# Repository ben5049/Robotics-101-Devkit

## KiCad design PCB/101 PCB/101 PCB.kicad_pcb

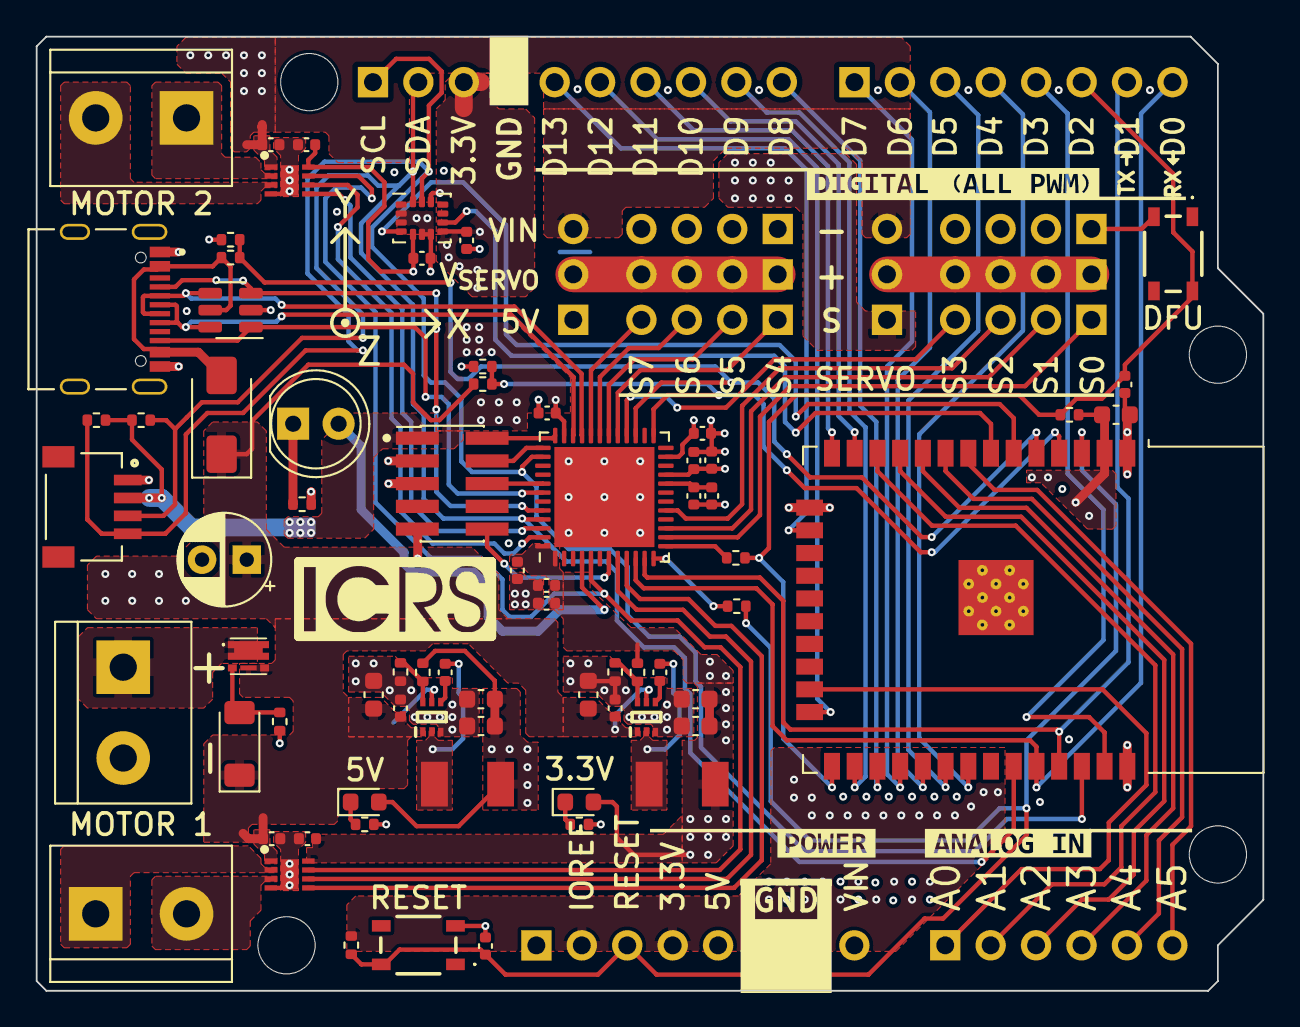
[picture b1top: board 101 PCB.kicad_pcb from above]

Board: 4 copper layers, 68.6 x 53.3 mm, 84 parts (1 on the bottom side), 74 nets.

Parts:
A101: Arduino_UNO_R3; ICRS_101_UNO_R3_NO_PINS
C1, C101, C102, C107, C108, C111, C112, C113, C114, C115, C116, C117, C118, C120, C121, C122, C123, C126: 100n; C_0402_1005Metric
C2, C103, C104, C105, C106, C109, C110: 22u; C_0603_1608Metric
C119: 47u; CP_Radial_D5.0mm_P2.50mm
C124: 4u7; C_0402_1005Metric
C125, C127: 1u; C_0402_1005Metric
D1: LED_R; LED_D5.0mm
D2: SK34
D101, D102: GREEN; LED_0603_1608Metric
D104: ZMM10V; D_MiniMELF
IC101, IC103: TPS563202DRLR; SOTFL50P160X60-6N
IC104, IC105: DRV8837DSGR; SON50P200X200X80-9N
J1: Conn_01x10; PinHeader_1x10_P2.54mm_Vertical
J2: Conn_ARM_JTAG_SWD_10; PinHeader_2x05_P1.27mm_Vertical_SMD
J3, J4: Conn_01x08; PinHeader_1x08_P2.54mm_Vertical
J5: Conn_01x06; PinHeader_1x06_P2.54mm_Vertical
J101: TYPE-C-31-M-12; HRO_TYPE-C-31-M-12
J102, J103, J110: Screw_Terminal_01x02; TerminalBlock_bornier-2_P5.08mm
J104, J105, J106, J107, J108, J109: Conn_01x04; PinHeader_1x04_P2.54mm_Vertical
J111: SM04B-SRSS-TB(LF)(SN); JST_SM04B-SRSS-TB(LF)(SN)
JP101, JP102: Jumper_3_Bridged12; PinHeader_1x03_P2.54mm_Vertical
L101: 4u7; L_Chilisin_BMRA00040415
L102: 3u3; L_Chilisin_BMRA00040415
Q101: DMP3028LFDE; DMP2066UFDE7
R1, R107, R109, R111: 10k; R_0402_1005Metric
R2, R3, R106, R108, R114: 330R; R_0402_1005Metric
R4, R5: 2k2; R_0402_1005Metric
R101: 27k; R_0402_1005Metric
R102, R105: 5k1; R_0402_1005Metric
R103: 1k2; R_0402_1005Metric
R104: 16k; R_0402_1005Metric
R110, R112: 1k; R_0402_1005Metric
S101, S102: TS20-42-25-WT-160-SMT-TR; TS204225WT160SMTTRMSL
U101: ESP32-WROOM-32
U103: USBLC6-4SC6-ES; SOT-23-6
U104: LSM6DS3; LGA-14_3x2.5mm_P0.5mm_LayoutBorder3x4y
U106: STM32G431CBUx; QFN-48-1EP_7x7mm_P0.5mm_EP5.6x5.6mm

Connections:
+3.3V: C2.1, C109.1, C110.1, C111.1, C112.1, C113.1, C115.1, C117.1, C120.1, C121.1, C122.1, C123.1, C124.1, C125.1, D102.2 (A), IC104.8 (VCC), IC105.8 (VCC), J1.3, J2.1 (VTref), J4.2, J4.4, J111.2, L102.2, R1.2, R4.2, R5.2, R104.1, R107.2, U101.2 (VDD), U104.5 (VDDIO), U104.8 (VDD), U104.12 (CS), U106.1 (VBAT), U106.21 (VDDA), U106.23 (VDD), U106.35 (VDD), U106.48 (VDD)
+5V: C103.1, C104.1, D101.2 (A), J4.5, JP101.1 (A), JP102.1 (A), L101.2, R101.1
+BATT: J110.1, Q101.1 (D_1), Q101.2 (D_2), Q101.5 (D_3), Q101.6 (D_4), Q101.8 (D_5)
/3V3_BST: C108.1, IC103.4 (BST)
/3V3_FB: IC103.6 (FB), R104.2, R105.1
/3V3_LED_K: D102.1 (K), R106.1
/3V3_SW: C108.2, IC103.2 (SW), L102.1
/5V_BST: C101.1, IC101.4 (BST)
/5V_FB: IC101.6 (FB), R101.2, R102.1
/5V_LED_K: D101.1 (K), R103.1
/5V_SW: C101.2, IC101.2 (SW), L101.1
/M1_OUT1: IC104.2 (OUT1), J102.1
/M1_OUT2: IC104.3 (OUT2), J102.2
/M2_OUT1: IC105.2 (OUT1), J103.1
/M2_OUT2: IC105.3 (OUT2), J103.2
/RP_PMOS_G: D104.2 (A), Q101.3 (G), R108.1
/STM32_EN: R114.1, U106.12 (PA4)
/STM32_IO0: R2.1, U106.13 (PA5)
/STM_LED_A: D1.2 (A), U106.4 (PC15)
/STM_LED_K: D1.1 (K), R3.2
CC1: J101.A5 (CC1), U103.3 (IO2), U106.44 (PB6)
CC2: J101.B5 (CC2), U103.1 (IO1), U106.42 (PB4)
EN: C118.1, J4.3, R107.1, R114.2, S101.2 (NO_2), U101.3 (EN)
ESP32_RX: J3.8, U101.34 (RXD0/IO3), U106.10 (PA2)
ESP32_TX: J3.7, U101.35 (TXD0/IO1), U106.11 (PA3)
GND: C1.2, C2.2, C102.2, C103.2, C104.2, C105.2, C106.2, C107.2, C109.2, C110.2, C111.2, C112.2, C113.2, C114.2, C115.2, C116.2, C117.2, C118.2, C119.2, C120.2, C121.2, C122.2, C123.2, C124.2, C125.2, C126.2, C127.2, IC101.3 (GND), IC103.3 (GND), IC104.4 (GND), IC104.9 (GND), IC105.4 (GND), IC105.9 (GND), J1.4, J2.3 (GND), J2.5 (GND), J2.9 (GNDDetect), J4.6, J4.7, J101.A1_B12 (GND), J101.B1_A12 (GND), J108.1, J108.2, J108.3, J108.4, J109.1, J109.2, J109.3, J109.4, J110.2, J111.1, R3.1, R102.2, R103.2, R105.2, R106.2, R108.2, R110.2, R112.2, S101.3 (COM_1), S102.3 (COM_1), U101.1 (GND), U101.15 (GND), U101.38 (GND), U101.39 (GND), U103.2 (GND), U104.1 (SDO/SA0), U104.2 (SDX), U104.3 (SCX), U104.6 (GND), U104.7 (GND), U106.49 (VSS)
GPIO2: J1.6, U101.24 (IO2)
GPIO4: J1.9, U101.26 (IO4)
GPIO5: J3.2, U101.29 (IO5)
GPIO12: J1.7, U101.14 (IO12)
GPIO13: J1.5, U101.16 (IO13)
GPIO14: J1.8, U101.13 (IO14)
GPIO15: J5.1, U101.23 (IO15)
GPIO16: J1.10, U101.27 (IO16)
GPIO17: J3.1, U101.28 (IO17)
GPIO18: J3.3, U101.30 (IO18)
GPIO19: J3.4, U101.31 (IO19)
GPIO23: J3.5, U101.37 (IO23)
GPIO25: J5.4, U101.10 (IO25)
GPIO26: J5.3, U101.11 (IO26)
GPIO27: J5.2, U101.12 (IO27)
GPIO32: J5.6, U101.8 (IO32)
GPIO33: J5.5, U101.9 (IO33)
IMU_INT1: U101.6 (IO34), U104.4 (INT1)
IMU_INT2: U101.7 (IO35), U104.9 (INT2)
IO0: C1.1, J3.6, R1.1, R2.2, S102.2 (NO_2), U101.25 (IO0)
M1_IN1: IC104.6 (IN1), U106.8 (PA0)
M1_IN2: IC104.5 (IN2), U106.9 (PA1)
M2_IN1: IC105.6 (IN1), U106.47 (PB9)
M2_IN2: IC105.5 (IN2), U106.46 (PB8)
MOTOR_SLEEP: IC104.7 (~SLEEP), IC105.7 (~SLEEP), U106.5 (PF0)
NRST: J2.10 (~RESET), U106.7 (PG10)
S0: J104.1, U106.14 (PA6)
S1: J104.2, U106.15 (PA7)
S2: J104.3, U106.17 (PB0)
S3: J104.4, U106.28 (PB15)
S4: J105.1, U106.29 (PC6)
S5: J105.2, U106.30 (PA8)
S6: J105.3, U106.31 (PA9)
S7: J105.4, U106.32 (PA10)
SCL: J1.1, J111.4, R5.1, U101.36 (IO22), U104.13 (SCL), U106.38 (PA15)
SDA: J1.2, J111.3, R4.1, U101.33 (IO21), U104.14 (SDA), U106.45 (PB7)
SWCLK: J2.4 (SWDCLK/TCK), U106.37 (PA14)
SWDIO: J2.2 (SWDIO/TMS), U106.36 (PA13)
SWO: J2.6 (SWO/TDO), U106.41 (PB3)
USB_DN: J101.A7 (DN1), J101.B7 (DN2), U103.4 (IO3), U106.33 (PA11)
USB_DP: J101.A6 (DP1), J101.B6 (DP2), U103.6 (IO4), U106.34 (PA12)
VBUS: D2.2 (A), J101.A4_B9 (VBUS), J101.B4_A9 (VBUS), R109.1, U103.5 (VBUS)
VBUS/11: R109.2, R110.1, U101.5 (SENSOR_VN), U106.27 (PB14)
VDDIO1: J106.1, J106.2, J106.3, J106.4, JP101.2 (C)
VDDIO2: J107.1, J107.2, J107.3, J107.4, JP102.2 (C)
VIN: C102.1, C105.1, C106.1, C107.1, C114.1, C116.1, C119.1, D2.1 (K), D104.1 (K), IC101.1 (VIN), IC101.5 (EN), IC103.1 (VIN), IC103.5 (EN), IC104.1 (VM), IC105.1 (VM), J4.8, JP101.3 (B), JP102.3 (B), Q101.4 (S_1), Q101.7 (S_2), R111.1
VIN/11: R111.2, R112.1, U101.4 (SENSOR_VP), U106.25 (PB12)
VREF+: C126.1, C127.1, U106.20 (VREF+)

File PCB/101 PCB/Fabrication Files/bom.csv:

Designator,Footprint,Quantity,Value,JLCPCB Part #（optional）
"C1, C101, C102, C107, C108, C111, C112, C113, C114, C115, C116, C117, C118, C120, C121, C122, C123, C126",402,18,100n,
"C103, C104, C105, C106, C109, C110, C2",603,7,22u,
C124,402,1,4u7,
"C125, C127",402,2,1u,
"D101, D102",603,2,GREEN,C965804
D104,D_MiniMELF,1,ZMM10V,C2891751
D2,SK34,1,SK34,C5140034
"IC101, IC103",SOTFL50P160X60-6N,2,TPS563202DRLR,C1513007
"IC104, IC105",SON50P200X200X80-9N,2,DRV8837DSGR,C39159
J1,PinHeader_1x10_P2.54mm_Vertical,1,Conn_01x10,C2905418
J101,HRO_TYPE-C-31-M-12,1,TYPE-C-31-M-12,C2765186
"J104, J105, J106, J107, J108, J109",PinHeader_1x04_P2.54mm_Vertical,6,Conn_01x04,C6332197
J111,JST_SM04B-SRSS-TB(LF)(SN),1,SM04B-SRSS-TB(LF)(SN),C7430446
J2,PinHeader_2x05_P1.27mm_Vertical_SMD,1,Conn_ARM_JTAG_SWD_10,C2881910
"J3, J4",PinHeader_1x08_P2.54mm_Vertical,2,Conn_01x08,C27438
J5,PinHeader_1x06_P2.54mm_Vertical,1,Conn_01x06,C40877
"JP101, JP102",PinHeader_1x03_P2.54mm_Vertical,2,Jumper_3_Bridged12,C2937625
L101,L_Chilisin_BMRA00040415,1,4u7,C3040385
L102,L_Chilisin_BMRA00040415,1,3u3,C3040384
Q101,DMP2066UFDE7,1,DMP3028LFDE,C150441
"R1, R107, R109, R111",402,4,10k,
R101,402,1,27k,
"R102, R105",402,2,5k1,
R103,402,1,1k2,
R104,402,1,16k,
"R106, R108, R114, R2, R3",402,5,330R,
"R110, R112",402,2,1k,
"R4, R5",402,2,2k2,
"S101, S102",TS204225WT160SMTTRMSL,2,TS20-42-25-WT-160-SMT-TR,C139797
U101,ESP32-WROOM-32,1,ESP32-WROOM-32,C701342
U103,SOT-23-6,1,USBLC6-4SC6-ES,C5180279
U104,LGA-14_3x2.5mm_P0.5mm_LayoutBorder3x4y,1,LSM6DS3,C967633
U106,QFN-48-1EP_7x7mm_P0.5mm_EP5.6x5.6mm,1,STM32G431CBUx,C529356

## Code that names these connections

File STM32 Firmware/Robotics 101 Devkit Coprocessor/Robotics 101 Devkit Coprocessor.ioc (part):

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Mcu.Name=STM32G431C(6-8-B)Ux
Mcu.Package=UFQFPN48
Mcu.UserName=STM32G431CBUx
PA0.Signal=S_TIM2_CH1
PA1.Signal=S_TIM2_CH2
PA11.Mode=Device
PA11.Signal=USB_DM
PA12.Mode=Device
PA12.Signal=USB_DP
PA13.Mode=Trace_Asynchronous_SW
PA13.Signal=SYS_JTMS-SWDIO
PA14.Mode=Trace_Asynchronous_SW
PA14.Signal=SYS_JTCK-SWCLK
PA15.Mode=I2C
PA15.Signal=I2C1_SCL
PA2.Mode=Asynchronous
PA2.Signal=USART2_TX
PA3.Mode=Asynchronous
PA3.Signal=USART2_RX
PA4.Mode=NSS_Signal_Hard_Output
PA4.Signal=SPI3_NSS
PA6.Signal=S_TIM3_CH1
PA7.Signal=S_TIM3_CH2
PB0.Signal=S_TIM3_CH3
PB1.Signal=S_TIM3_CH4
PB10.Signal=S_TIM2_CH3
PB11.Signal=S_TIM2_CH4
PB15.Mode=IN15-Single-Ended
PB15.Signal=ADC2_IN15
PB3.Mode=Trace_Asynchronous_SW
PB3.Signal=SYS_JTDO-SWO
PB4.Mode=Sink_AllSignals
PB4.Signal=UCPD1_CC2
PB5.Mode=Full_Duplex_Master
PB5.Signal=SPI3_MOSI
PB6.Mode=Sink_AllSignals
PB6.Signal=UCPD1_CC1
PB7.Mode=I2C
PB7.Signal=I2C1_SDA
PB8-BOOT0.Signal=S_TIM8_CH2
PB9.Signal=S_TIM8_CH3
PC10.Mode=Full_Duplex_Master
PC10.Signal=SPI3_SCK
PC11.Mode=Full_Duplex_Master
PC11.Signal=SPI3_MISO
PC13.Mode=PWM Generation4 CH4N
PC13.Signal=TIM8_CH4N
PC6.Signal=S_TIM8_CH1
PF0-OSC_IN.Mode=IN10-Single-Ended
PF0-OSC_IN.Signal=ADC1_IN10
RCC.HSE_VALUE=8000000
RCC.SYSCLKFreq_VALUE=144000000
RCC.SYSCLKSource=RCC_SYSCLKSOURCE_PLLCLK
board=custom

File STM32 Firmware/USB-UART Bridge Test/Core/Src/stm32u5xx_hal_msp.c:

/* USER CODE BEGIN Header */
/**
  ******************************************************************************
  * @file         stm32u5xx_hal_msp.c
  * @brief        This file provides code for the MSP Initialization
  *               and de-Initialization codes.
  ******************************************************************************
  * @attention
  *
  * Copyright (c) 2023 STMicroelectronics.
  * All rights reserved.
  *
  * This software is licensed under terms that can be found in the LICENSE file
  * in the root directory of this software component.
  * If no LICENSE file comes with this software, it is provided AS-IS.
  *
  ******************************************************************************
  */
/* USER CODE END Header */

/* Includes ------------------------------------------------------------------*/
#include "main.h"
/* USER CODE BEGIN Includes */

/* USER CODE END Includes */

/* Private typedef -----------------------------------------------------------*/
/* USER CODE BEGIN TD */

/* USER CODE END TD */

/* Private define ------------------------------------------------------------*/
/* USER CODE BEGIN Define */

/* USER CODE END Define */

/* Private macro -------------------------------------------------------------*/
/* USER CODE BEGIN Macro */

/* USER CODE END Macro */

/* Private variables ---------------------------------------------------------*/
/* USER CODE BEGIN PV */

/* USER CODE END PV */

/* Private function prototypes -----------------------------------------------*/
/* USER CODE BEGIN PFP */

/* USER CODE END PFP */

/* External functions --------------------------------------------------------*/
/* USER CODE BEGIN ExternalFunctions */

/* USER CODE END ExternalFunctions */

/* USER CODE BEGIN 0 */

/* USER CODE END 0 */
/**
  * Initializes the Global MSP.
  */
void HAL_MspInit(void)
{
  /* USER CODE BEGIN MspInit 0 */

  /* USER CODE END MspInit 0 */

  __HAL_RCC_PWR_CLK_ENABLE();

  HAL_NVIC_SetPriorityGrouping(NVIC_PRIORITYGROUP_3);

  /* System interrupt init*/

  /* USER CODE BEGIN MspInit 1 */

  /* USER CODE END MspInit 1 */
}

/**
* @brief ADC MSP Initialization
* This function configures the hardware resources used in this example
* @param hadc: ADC handle pointer
* @retval None
*/
void HAL_ADC_MspInit(ADC_HandleTypeDef* hadc)
{
  GPIO_InitTypeDef GPIO_InitStruct = {0};
  RCC_PeriphCLKInitTypeDef PeriphClkInit = {0};
  if(hadc->Instance==ADC1)
  {
  /* USER CODE BEGIN ADC1_MspInit 0 */

  /* USER CODE END ADC1_MspInit 0 */

  /** Initializes the peripherals clock
  */
    PeriphClkInit.PeriphClockSelection = RCC_PERIPHCLK_ADCDAC;
    PeriphClkInit.AdcDacClockSelection = RCC_ADCDACCLKSOURCE_HSI;
    if (HAL_RCCEx_PeriphCLKConfig(&PeriphClkInit) != HAL_OK)
    {
      Error_Handler();
    }

    /* Peripheral clock enable */
    __HAL_RCC_ADC12_CLK_ENABLE();

    __HAL_RCC_GPIOC_CLK_ENABLE();
    /**ADC1 GPIO Configuration
    PC2     ------> ADC1_IN3
    */
    GPIO_InitStruct.Pin = VBUS_SENSE_Pin;
    GPIO_InitStruct.Mode = GPIO_MODE_ANALOG;
    GPIO_InitStruct.Pull = GPIO_NOPULL;
    HAL_GPIO_Init(VBUS_SENSE_GPIO_Port, &GPIO_InitStruct);

  /* USER CODE BEGIN ADC1_MspInit 1 */

  /* USER CODE END ADC1_MspInit 1 */
  }

}

/**
* @brief ADC MSP De-Initialization
* This function freeze the hardware resources used in this example
* @param hadc: ADC handle pointer
* @retval None
*/
void HAL_ADC_MspDeInit(ADC_HandleTypeDef* hadc)
{
  if(hadc->Instance==ADC1)
  {
  /* USER CODE BEGIN ADC1_MspDeInit 0 */

  /* USER CODE END ADC1_MspDeInit 0 */
    /* Peripheral clock disable */
    __HAL_RCC_ADC12_CLK_DISABLE();

    /**ADC1 GPIO Configuration
    PC2     ------> ADC1_IN3
    */
    HAL_GPIO_DeInit(VBUS_SENSE_GPIO_Port, VBUS_SENSE_Pin);

  /* USER CODE BEGIN ADC1_MspDeInit 1 */

  /* USER CODE END ADC1_MspDeInit 1 */
  }

}

/**
* @brief UART MSP Initialization
* This function configures the hardware resources used in this example
* @param huart: UART handle pointer
* @retval None
*/
void HAL_UART_MspInit(UART_HandleTypeDef* huart)
{
  GPIO_InitTypeDef GPIO_InitStruct = {0};
  RCC_PeriphCLKInitTypeDef PeriphClkInit = {0};
  if(huart->Instance==USART1)
  {
  /* USER CODE BEGIN USART1_MspInit 0 */

  /* USER CODE END USART1_MspInit 0 */

  /** Initializes the peripherals clock
  */
    PeriphClkInit.PeriphClockSelection = RCC_PERIPHCLK_USART1;
    PeriphClkInit.Usart1ClockSelection = RCC_USART1CLKSOURCE_PCLK2;
    if (HAL_RCCEx_PeriphCLKConfig(&PeriphClkInit) != HAL_OK)
    {
      Error_Handler();
    }

    /* Peripheral clock enable */
    __HAL_RCC_USART1_CLK_ENABLE();

    __HAL_RCC_GPIOA_CLK_ENABLE();
    /**USART1 GPIO Configuration
    PA9     ------> USART1_TX
    PA10     ------> USART1_RX
    */
    GPIO_InitStruct.Pin = USART1_TX_Pin|USART1_RX_Pin;
    GPIO_InitStruct.Mode = GPIO_MODE_AF_PP;
    GPIO_InitStruct.Pull = GPIO_PULLDOWN;
    GPIO_InitStruct.Speed = GPIO_SPEED_FREQ_VERY_HIGH;
    GPIO_InitStruct.Alternate = GPIO_AF7_USART1;
    HAL_GPIO_Init(GPIOA, &GPIO_InitStruct);

  /* USER CODE BEGIN USART1_MspInit 1 */

  /* USER CODE END USART1_MspInit 1 */
  }

}

/**
* @brief UART MSP De-Initialization
* This function freeze the hardware resources used in this example
* @param huart: UART handle pointer
* @retval None
*/
void HAL_UART_MspDeInit(UART_HandleTypeDef* huart)
{
  if(huart->Instance==USART1)
  {
  /* USER CODE BEGIN USART1_MspDeInit 0 */

  /* USER CODE END USART1_MspDeInit 0 */
    /* Peripheral clock disable */
    __HAL_RCC_USART1_CLK_DISABLE();

    /**USART1 GPIO Configuration
    PA9     ------> USART1_TX
    PA10     ------> USART1_RX
    */
    HAL_GPIO_DeInit(GPIOA, USART1_TX_Pin|USART1_RX_Pin);

  /* USER CODE BEGIN USART1_MspDeInit 1 */

  /* USER CODE END USART1_MspDeInit 1 */
  }

}

/**
* @brief PCD MSP Initialization
* This function configures the hardware resources used in this example
* @param hpcd: PCD handle pointer
* @retval None
*/
void HAL_PCD_MspInit(PCD_HandleTypeDef* hpcd)
{
  GPIO_InitTypeDef GPIO_InitStruct = {0};
  RCC_PeriphCLKInitTypeDef PeriphClkInit = {0};
  if(hpcd->Instance==USB_OTG_FS)
  {
  /* USER CODE BEGIN USB_OTG_FS_MspInit 0 */

  /* USER CODE END USB_OTG_FS_MspInit 0 */

  /** Initializes the peripherals clock
  */
    PeriphClkInit.PeriphClockSelection = RCC_PERIPHCLK_CLK48;
    PeriphClkInit.IclkClockSelection = RCC_CLK48CLKSOURCE_HSI48;
    if (HAL_RCCEx_PeriphCLKConfig(&PeriphClkInit) != HAL_OK)
    {
      Error_Handler();
    }

    __HAL_RCC_GPIOA_CLK_ENABLE();
    /**USB_OTG_FS GPIO Configuration
    PA11     ------> USB_OTG_FS_DM
    PA12     ------> USB_OTG_FS_DP
    */
    GPIO_InitStruct.Pin = USB_OTG_FS_DM_Pin|USB_OTG_FS_DP_Pin;
    GPIO_InitStruct.Mode = GPIO_MODE_AF_PP;
    GPIO_InitStruct.Pull = GPIO_NOPULL;
    GPIO_InitStruct.Speed = GPIO_SPEED_FREQ_VERY_HIGH;
    GPIO_InitStruct.Alternate = GPIO_AF10_USB;
    HAL_GPIO_Init(GPIOA, &GPIO_InitStruct);

    /* Peripheral clock enable */
    __HAL_RCC_USB_CLK_ENABLE();

    /* Enable VDDUSB */
    if(__HAL_RCC_PWR_IS_CLK_DISABLED())
    {
      __HAL_RCC_PWR_CLK_ENABLE();
      HAL_PWREx_EnableVddUSB();
      __HAL_RCC_PWR_CLK_DISABLE();
    }
    else
    {
      HAL_PWREx_EnableVddUSB();
    }
    /* USB_OTG_FS interrupt Init */
    HAL_NVIC_SetPriority(OTG_FS_IRQn, 0, 0);
    HAL_NVIC_EnableIRQ(OTG_FS_IRQn);
  /* USER CODE BEGIN USB_OTG_FS_MspInit 1 */

  /* USER CODE END USB_OTG_FS_MspInit 1 */
  }

}

/**
* @brief PCD MSP De-Initialization
* This function freeze the hardware resources used in this example
* @param hpcd: PCD handle pointer
* @retval None
*/
void HAL_PCD_MspDeInit(PCD_HandleTypeDef* hpcd)
{
  if(hpcd->Instance==USB_OTG_FS)
  {
  /* USER CODE BEGIN USB_OTG_FS_MspDeInit 0 */

  /* USER CODE END USB_OTG_FS_MspDeInit 0 */
    /* Peripheral clock disable */
    __HAL_RCC_USB_CLK_DISABLE();

    /**USB_OTG_FS GPIO Configuration
    PA11     ------> USB_OTG_FS_DM
    PA12     ------> USB_OTG_FS_DP
    */
    HAL_GPIO_DeInit(GPIOA, USB_OTG_FS_DM_Pin|USB_OTG_FS_DP_Pin);

    /* USB_OTG_FS interrupt DeInit */
    HAL_NVIC_DisableIRQ(OTG_FS_IRQn);
  /* USER CODE BEGIN USB_OTG_FS_MspDeInit 1 */

  /* USER CODE END USB_OTG_FS_MspDeInit 1 */
  }

}

/* USER CODE BEGIN 1 */

/* USER CODE END 1 */

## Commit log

2023-07-05 Added PCB and STM32 firmware
2023-07-07 Board layout done
2023-09-11 Firmware working
